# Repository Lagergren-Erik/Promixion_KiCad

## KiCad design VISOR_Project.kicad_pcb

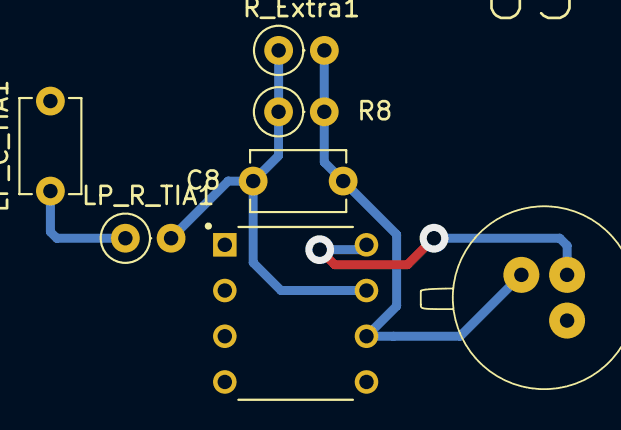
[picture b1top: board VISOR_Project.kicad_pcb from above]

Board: 2 copper layers, 7 parts (0 on the bottom side), 5 nets.

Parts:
C8: 20p; C_Disc_D5.1mm_W3.2mm_P5.00mm
LP_C_TIA1: C_Disc_D5.1mm_W3.2mm_P5.00mm
LP_R_TIA1: R_Axial_DIN0207_L6.3mm_D2.5mm_P2.54mm_Vertical
R8: 1.5k; R_Axial_DIN0207_L6.3mm_D2.5mm_P2.54mm_Vertical
R_Extra1: 0; R_Axial_DIN0207_L6.3mm_D2.5mm_P2.54mm_Vertical
U5: MCP6002-I_P; DIP787W46P254L927H533Q8
U6: INGaAS_Photodiode

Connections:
+5V: U5.8 (VDD), U6.2 (PD-)
/ADC: LP_C_TIA1.2, LP_R_TIA1.1
GND: LP_C_TIA1.1, U5.5 (VINB+), U6.1 (CASE)
unnamed: C8.1, R8.2, R_Extra1.2, U5.6 (VINB-), U6.3 (PD+)
unnamed: C8.2, LP_R_TIA1.2, R8.1, R_Extra1.1, U5.7 (VOUTB)

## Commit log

2025-11-04 Initial commit från KiCad-projektet
2025-11-07 Uppdaterat KiCad-projekt med senaste ändringar
2025-11-18 project name
2025-11-18 Laser comonent added
2025-11-18 SPDT added
2025-11-18 test
2025-11-19 circuit config
2025-11-19 TIA fix
2025-11-20 Schematic update
